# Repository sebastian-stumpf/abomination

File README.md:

# abomination

## Attention

I'm a hobbyist/amateur at best. So there may be things that aren't optimized. That being said I've had the files
in the `gerbers/` directory manufactured at JLC with 1.6mm thickness and they work just fine with my fork of the qmk repository
directory. So if you decide to use this, then please be advised that I'm not providing any sort of liability and you should
exercise some caution.

## Trackpad

The trackpad relies on the following adapter https://github.com/keyboard-magpie/minimal-fpc-i2c-pcb/ which can cheapily be PCBA'ed.
There reasons for using this adapter are that I hate soldering those tiny clamshell connectors and I can easily hot swap the
trackpad with an OLED display.

## Case

There are two plate versions for the case. The default version is very thin and wobbly and the switches aren't pressed in easily.
There's also a 'thick' version of the plates that sits on the pcb rock solid and the switches pop in with ease. I'd heavily recommend
the thick version. Just be aware that it will consume about 4 times the material as the thin plate.

## BOM

| Quantity   | Item                               | Comment                  |
| ---------  | ---------------------------------- | ------------------------ |
| 2          | Helios or Liatris Controller       |                          |
| 2          | IC-Sockets for MCU                 | Optional but recommended |
| 2          | TRRS Sockets                       |                          |
| 40         | 1N4148 SOD123 diodes               |                          |
| 2          | SKHLLBA010 buttons                 |                          |
| 36         | MX Hotswap Sockets                 |                          |
| 1          | EC12 Encoders                      |                          |
| 4          | 6mm tactile switches               | Longer caps work best    |
| 36         | MX Switches + Keycaps              |                          |
| 1          | Cirque 40mm curved trackpad        | Desolder R1 for i2c      |
| 1          | i2c adapter PCB for trackpad       | see above                |
| 1          | fpc cable for adapter              |                          |
| 1          | 4 pin dip socket and header        | for the adapter          |
| a lot      | M2 Screws (flat & countersunk)     |                          |
| also a lot | M2 heat inserts                    |                          |
| 12         | round bumpons with 3,1mm dia       |                          |

## Firmware

See [my fork](https://github.com/sebastian-stumpf/qmk_firmware/tree/sepp/keyboards/abomination) of the qmk repository. Nothing special here.
You can just copy the code over to your own repository and adjust the keymap.

## Feedback

I'm always happy to hear your opinions about this and if you decide to build this board then please do send me a picture of it.

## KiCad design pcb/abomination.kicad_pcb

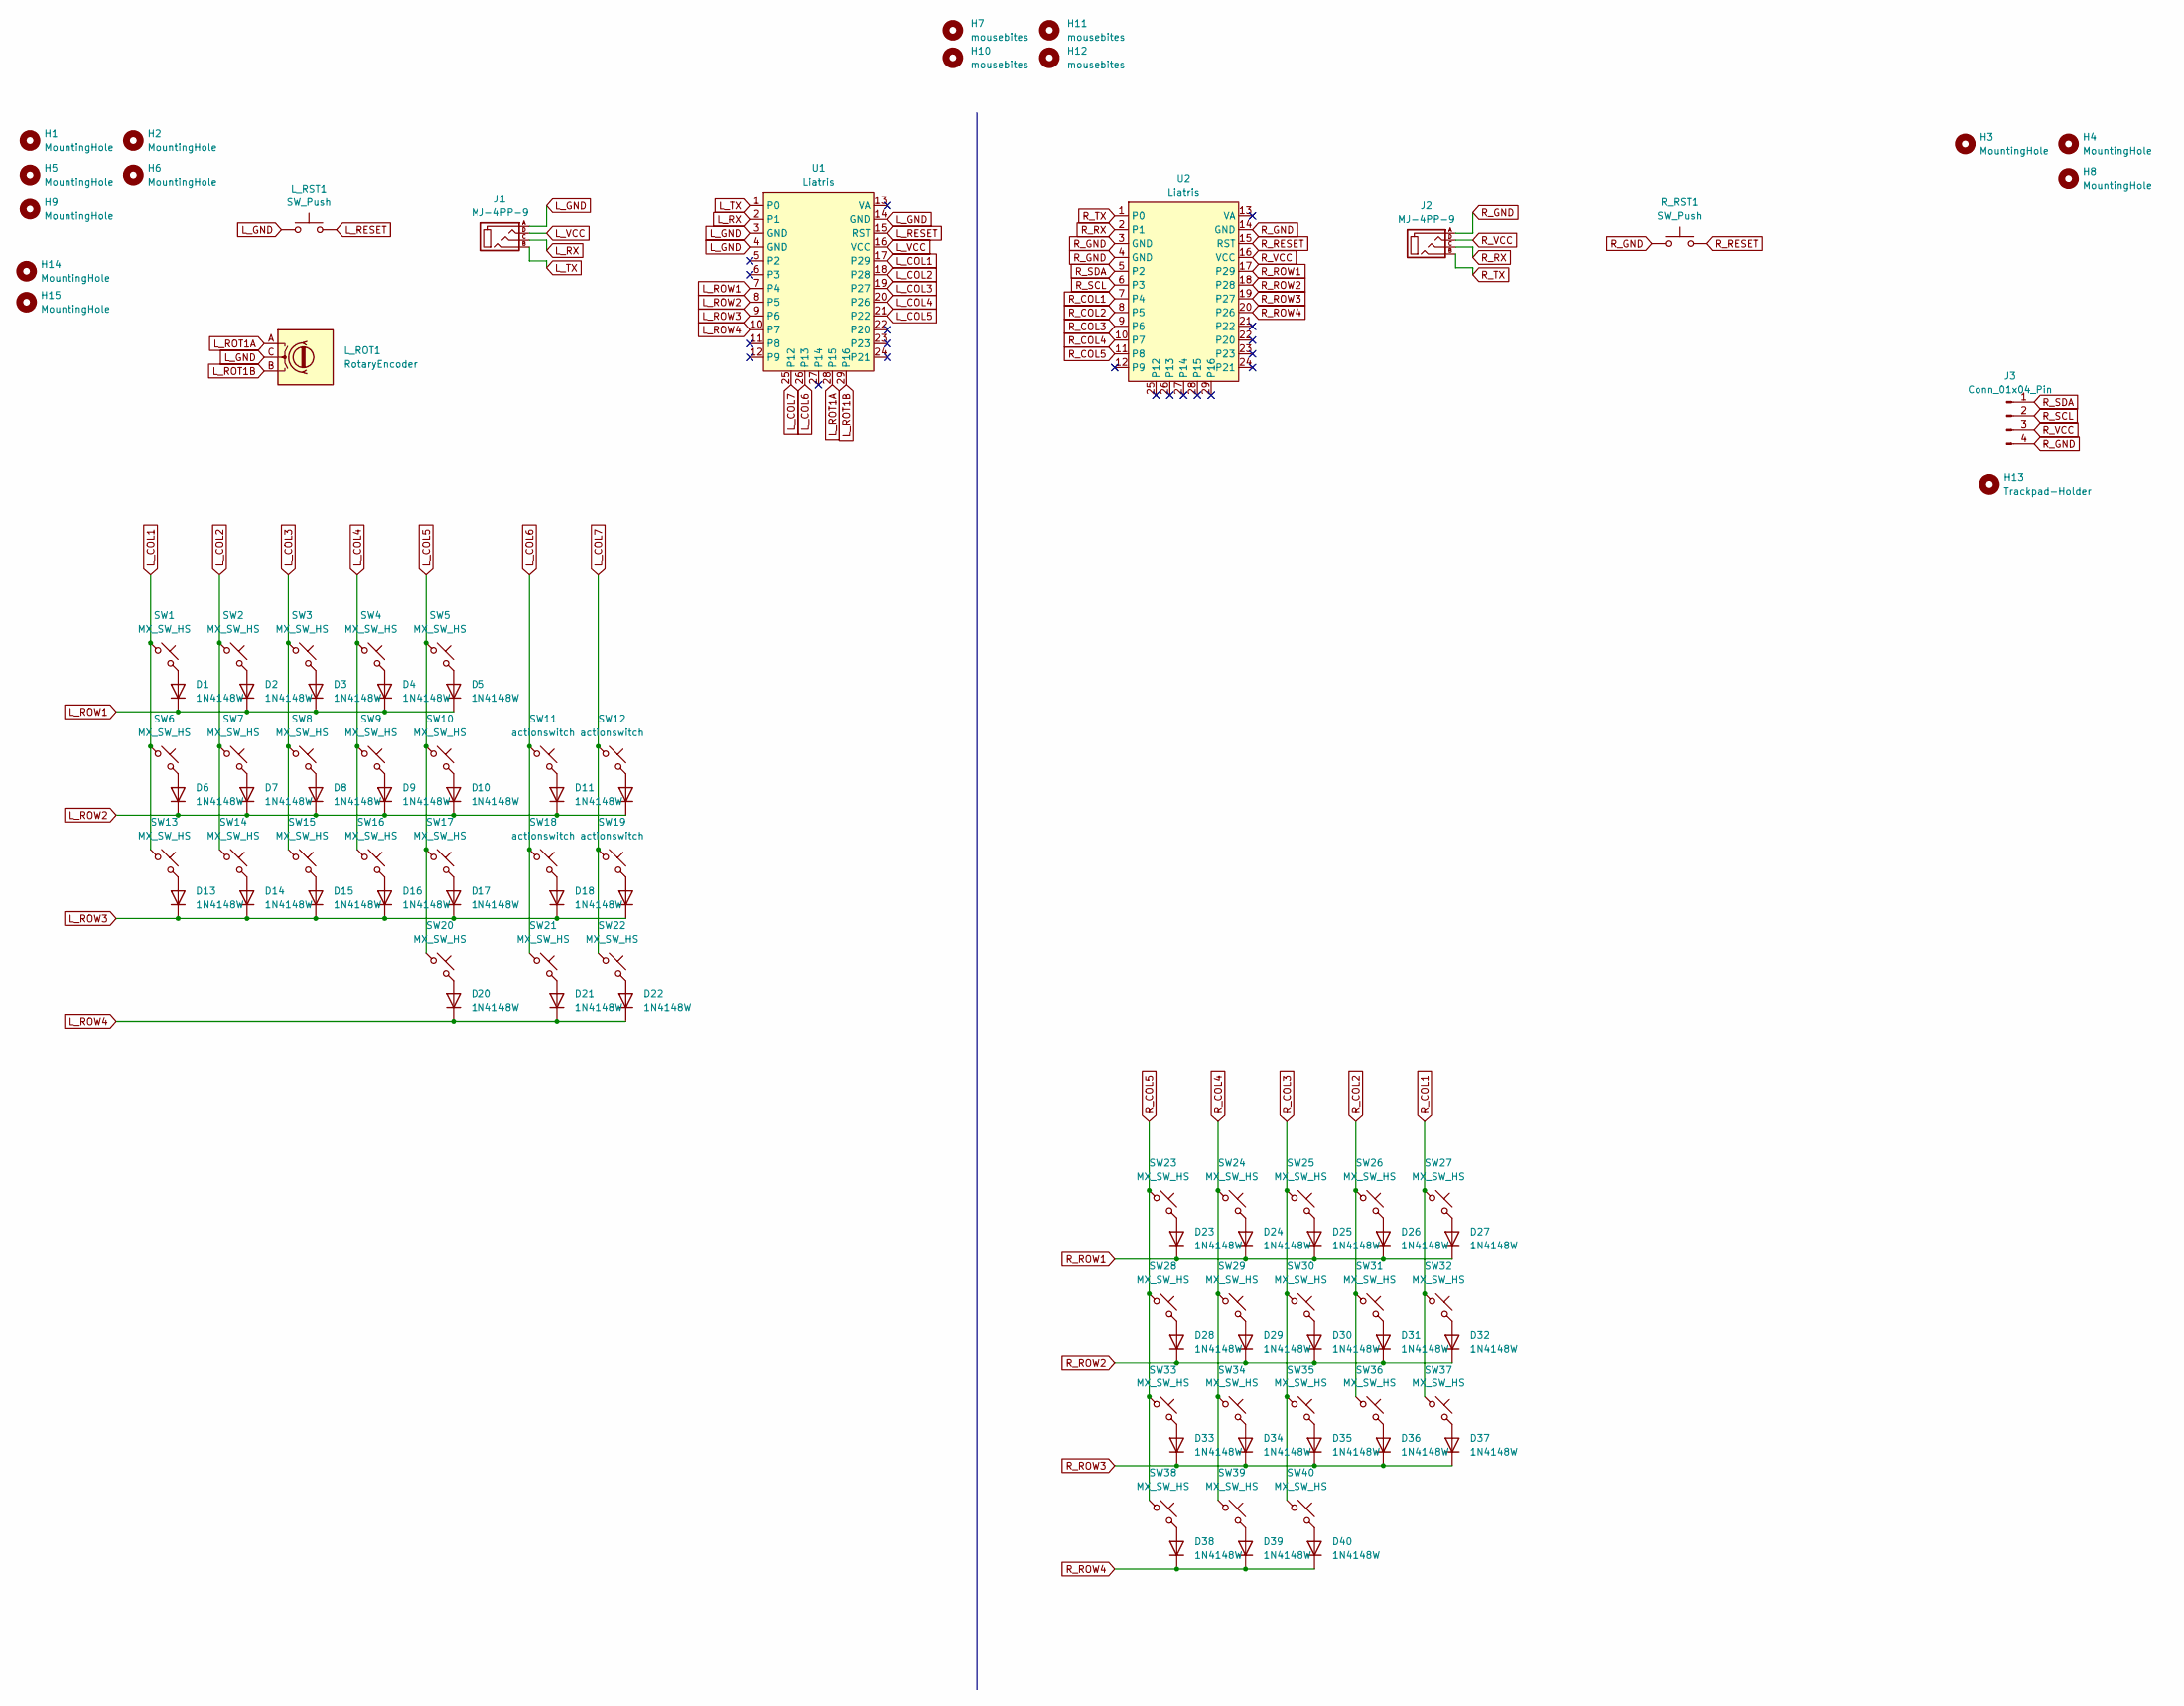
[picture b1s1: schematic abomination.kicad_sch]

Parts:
D1, D2, D3, D4, D5, D6, D7, D8, D9, D10, D11, D12, D13, D14, D15, D16, D17, D18, D19, D20, D21, D22, D23, D24, D25, D26, D27, D28, D29, D30, D31, D32, D33, D34, D35, D36, D37, D38, D39, D40: 1N4148W; D_SOD-123
H1, H2, H3, H4, H5, H6, H8, H9, H14, H15: MountingHole; MountingHole_2.2mm_M2_DIN965
H7, H10, H11, H12: mousebites; breakaway-mousebites
H13: Trackpad-Holder; abimination-trackpad-holder
J1, J2: MJ-4PP-9
J3: Conn_01x04_Pin; fpc-breakcout-connector
L_ROT1: RotaryEncoder; RotaryEncoder_Alps_EC12E_Vertical_H20mm
L_RST1: SW_Push; SW_SKHLLCA010
R_RST1: SW_Push; SW_SKHLLCA010
SW1, SW2, SW3, SW4, SW5, SW6, SW7, SW8, SW9, SW10, SW13, SW14, SW15, SW16, SW17, SW20, SW21, SW22, SW23, SW24, SW25, SW26, SW27, SW28, SW29, SW30, SW31, SW32, SW33, SW34, SW35, SW36, SW37, SW38, SW39, SW40: MX_SW_HS; SW_MX_HS_1u
SW11, SW12, SW18, SW19: actionswitch
U1, U2: Liatris; Liatris_AH_USBdn

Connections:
L_COL1: SW1.1, SW6.1, SW13.1, U1.17 (P29)
L_COL2: SW2.1, SW7.1, SW14.1, U1.18 (P28)
L_COL3: SW3.1, SW8.1, SW15.1, U1.19 (P27)
L_COL4: SW4.1, SW9.1, SW16.1, U1.20 (P26)
L_COL5: SW5.1, SW10.1, SW17.1, SW20.1, U1.21 (P22)
L_COL6: SW11.1, SW18.1, SW21.1, U1.26 (P13)
L_COL7: SW12.1, SW19.1, SW22.1, U1.25 (P12)
L_GND: J1.A, L_ROT1.C, L_RST1.1, U1.3 (GND), U1.4 (GND), U1.14 (GND)
L_RESET: L_RST1.2, U1.15 (RST)
L_ROT1A: L_ROT1.A, U1.28 (P15)
L_ROT1B: L_ROT1.B, U1.29 (P16)
L_ROW1: D1.1 (K), D2.1 (K), D3.1 (K), D4.1 (K), D5.1 (K), U1.7 (P4)
L_ROW2: D6.1 (K), D7.1 (K), D8.1 (K), D9.1 (K), D10.1 (K), D11.1 (K), D12.1 (K), U1.8 (P5)
L_ROW3: D13.1 (K), D14.1 (K), D15.1 (K), D16.1 (K), D17.1 (K), D18.1 (K), D19.1 (K), U1.9 (P6)
L_ROW4: D20.1 (K), D21.1 (K), D22.1 (K), U1.10 (P7)
L_RX: J1.C, U1.2 (P1)
L_TX: J1.B, U1.1 (P0)
L_VCC: J1.D, U1.16 (VCC)
unnamed: D1.2 (A), SW1.2
unnamed: D2.2 (A), SW2.2
unnamed: D3.2 (A), SW3.2
unnamed: D4.2 (A), SW4.2
unnamed: D5.2 (A), SW5.2
unnamed: D6.2 (A), SW6.2
unnamed: D7.2 (A), SW7.2
unnamed: D8.2 (A), SW8.2
unnamed: D9.2 (A), SW9.2
unnamed: D10.2 (A), SW10.2
unnamed: D11.2 (A), SW11.2
unnamed: D12.2 (A), SW12.2
unnamed: D13.2 (A), SW13.2
unnamed: D14.2 (A), SW14.2
unnamed: D15.2 (A), SW15.2
unnamed: D16.2 (A), SW16.2
unnamed: D17.2 (A), SW17.2
unnamed: D18.2 (A), SW18.2
unnamed: D19.2 (A), SW19.2
unnamed: D20.2 (A), SW20.2
unnamed: D21.2 (A), SW21.2
unnamed: D22.2 (A), SW22.2
unnamed: D23.2 (A), SW23.2
unnamed: D24.2 (A), SW24.2
unnamed: D25.2 (A), SW25.2
unnamed: D26.2 (A), SW26.2
unnamed: D27.2 (A), SW27.2
unnamed: D28.2 (A), SW28.2
unnamed: D29.2 (A), SW29.2
unnamed: D30.2 (A), SW30.2
unnamed: D31.2 (A), SW31.2
unnamed: D32.2 (A), SW32.2
unnamed: D33.2 (A), SW33.2
unnamed: D34.2 (A), SW34.2
unnamed: D35.2 (A), SW35.2
unnamed: D36.2 (A), SW36.2
unnamed: D37.2 (A), SW37.2
unnamed: D38.2 (A), SW38.2
unnamed: D39.2 (A), SW39.2
unnamed: D40.2 (A), SW40.2
R_COL1: SW27.1, SW32.1, SW37.1, U2.7 (P4)
R_COL2: SW26.1, SW31.1, SW36.1, U2.8 (P5)
R_COL3: SW25.1, SW30.1, SW35.1, SW40.1, U2.9 (P6)
R_COL4: SW24.1, SW29.1, SW34.1, SW39.1, U2.10 (P7)
R_COL5: SW23.1, SW28.1, SW33.1, SW38.1, U2.11 (P8)
R_GND: J2.A, J3.4, R_RST1.1, U2.3 (GND), U2.4 (GND), U2.14 (GND)
R_RESET: R_RST1.2, U2.15 (RST)
R_ROW1: D23.1 (K), D24.1 (K), D25.1 (K), D26.1 (K), D27.1 (K), U2.17 (P29)
R_ROW2: D28.1 (K), D29.1 (K), D30.1 (K), D31.1 (K), D32.1 (K), U2.18 (P28)
R_ROW3: D33.1 (K), D34.1 (K), D35.1 (K), D36.1 (K), D37.1 (K), U2.19 (P27)
R_ROW4: D38.1 (K), D39.1 (K), D40.1 (K), U2.20 (P26)
R_RX: J2.C, U2.2 (P1)
R_SCL: J3.2, U2.6 (P3)
R_SDA: J3.1, U2.5 (P2)
R_TX: J2.B, U2.1 (P0)
R_VCC: J2.D, J3.3, U2.16 (VCC)

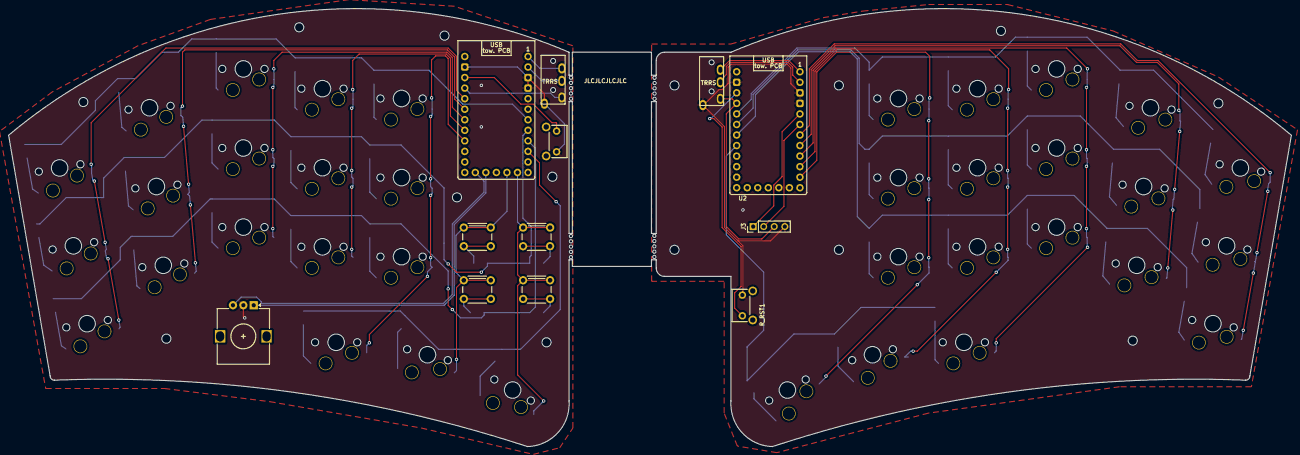
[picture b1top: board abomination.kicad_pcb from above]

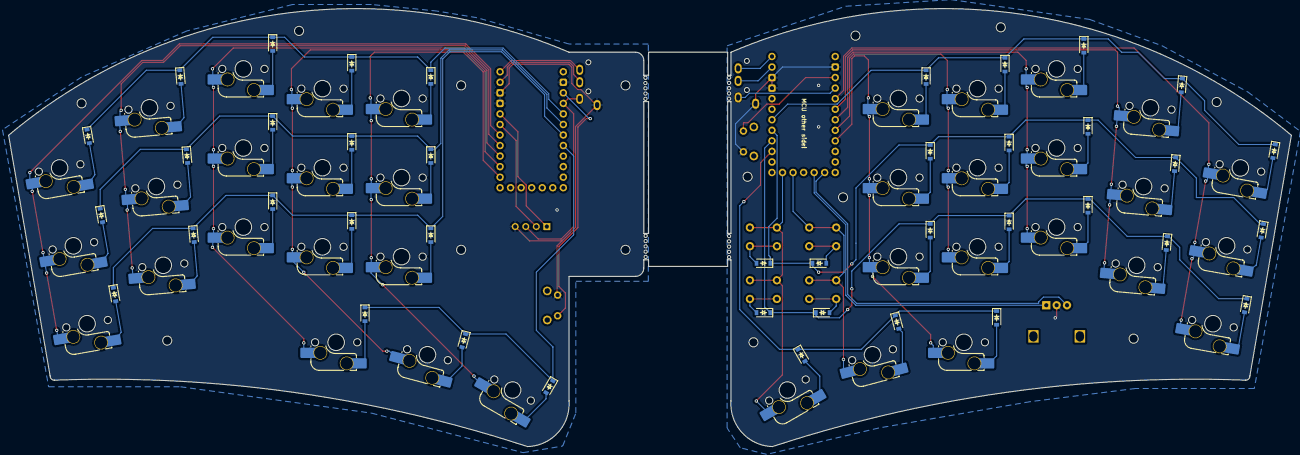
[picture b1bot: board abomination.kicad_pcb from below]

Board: 2 copper layers, 309.0 x 105.5 mm, 103 parts (40 on the bottom side), 74 nets.

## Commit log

2023-10-20 added new case
